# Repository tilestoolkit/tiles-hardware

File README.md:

# IoT Squares 

Squares are tiny stickers with electronics that give superpowers to everyday objects. They implement a set of physical interaction primitives.

Squares are part of Tiles, an inventor toolbox to support the design and making of interactive objects for learning and play. For more information tilestoolkit.io

This work is licensed under a [Creative Commons Attribution-ShareAlike 4.0 International License](https://creativecommons.org/licenses/by-sa/4.0/).

## Prototypes History

### Prototype 1
Designed by Norwegian Creation, March 2015

### Prototype 2 Rev A
Designed by Simone Mora, PCB manufacturing and partial assembly from Seeedstudio Fusion Service, November 2015
#### Note: 
* Bug in board design, shortcut between VDD and SDA lines

### Prototype 2 Rev B
Designed by Simone Mora, never produced.
#### Note: 
* Fixed Rev A bugs

### Prototype 2 Rev C
Designed by Simone Mora, PCB manufacturing and partial assembly from Seeedstudio Fusion Service, April 2016
#### Note: 
* Removed touch controller MPR121
* Swapped components no longer available from Seed CPL

### Prototype 2 Rev D
Designed by Simone Mora, PCB manufacturing and partial assembly from Macrofab, November 2016
#### Note:
* Moved from SMD to DIP programming header
* Swapped components not available on Macrofab common parts library
* Added Seeed GROVE I2C connector

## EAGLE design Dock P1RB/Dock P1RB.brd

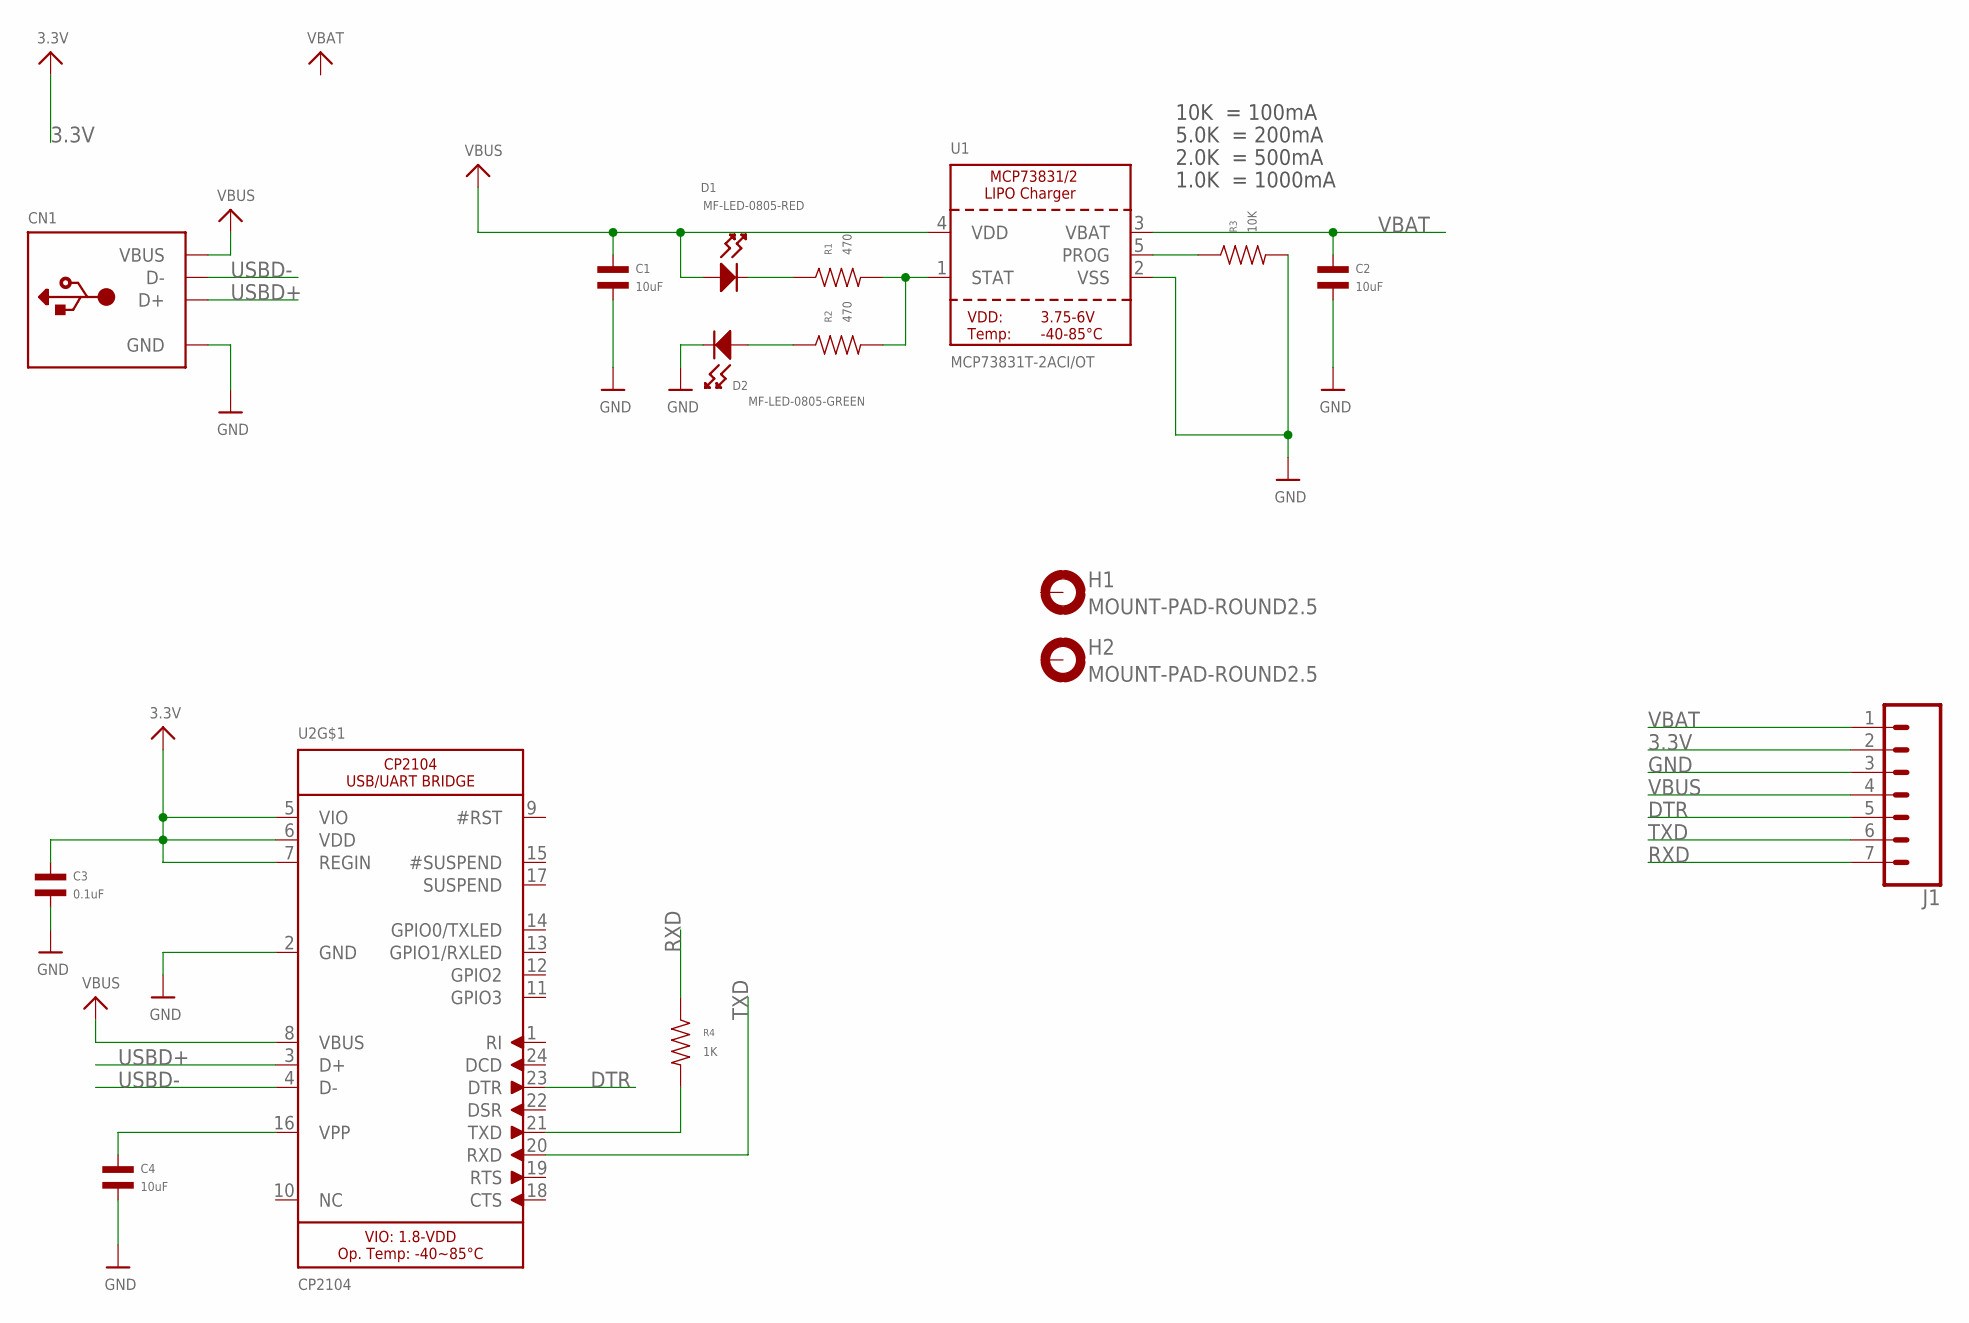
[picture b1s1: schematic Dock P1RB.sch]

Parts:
C1, C2, C4: 10uF; C1206; MPN MF-CAP-1206-10uF
C3: 0.1uF; C0603; MPN MF-CAP-0603-0.1uF
CN1: USB_TYPEAPCB; USBA_PCB
D1: MF-LED-0805-RED; LED0805
D2: MF-LED-0805-GREEN; LED0805
H1, H2: MOUNT-PAD-ROUND2.5; 2,5-PAD-SIM
J1: CONN_07; 1X07
R1, R2: 470; R0603; MPN MF-RES-0603-470
R3: 10K; R0603; MPN MF-RES-0603-10K
R4: 1K; R0603; MPN MF-RES-0603-1K
U1: MCP73831T-2ACI/OT; SOT23-5; MPN MCP73831T-2ACI/OT
U2: CP2104; QFN24_4MM_SMSC; MPN CP2104

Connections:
3.3V: C3.P$1, J1.2, U2.5 (VIO), U2.6 (VDD), U2.7 (REGIN)
DTR: J1.5, U2.23 (DTR)
GND: C1.P$2, C2.P$2, C3.P$2, C4.P$2, CN1.GND, D2.CATHODE, J1.3, R3.P$2, U1.2 (VSS), U2.2 (GND)
unnamed: D1.CATHODE, R1.P$1
unnamed: R1.P$2, R2.P$2, U1.1 (STAT)
unnamed: C4.P$1, U2.16 (VPP)
unnamed: R3.P$1, U1.5 (PROG)
unnamed: D2.ANODE, R2.P$1
unnamed: R4.P$2, U2.21 (TXD)
RXD: J1.7, R4.P$1
TP: U2.THERM (TP)
TXD: J1.6, U2.20 (RXD)
USBD+: CN1.USB_PLUS (D+), U2.3 (D+)
USBD-: CN1.USB_NEG (D-), U2.4 (D-)
VBAT: C2.P$1, J1.1, U1.3 (VBAT)
VBUS: C1.P$1, CN1.VCC (VBUS), D1.ANODE, J1.4, U1.4 (VDD), U2.8 (VBUS)

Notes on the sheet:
10K = 100mA
5.0K = 200mA
2.0K = 500mA
1.0K = 1000mA

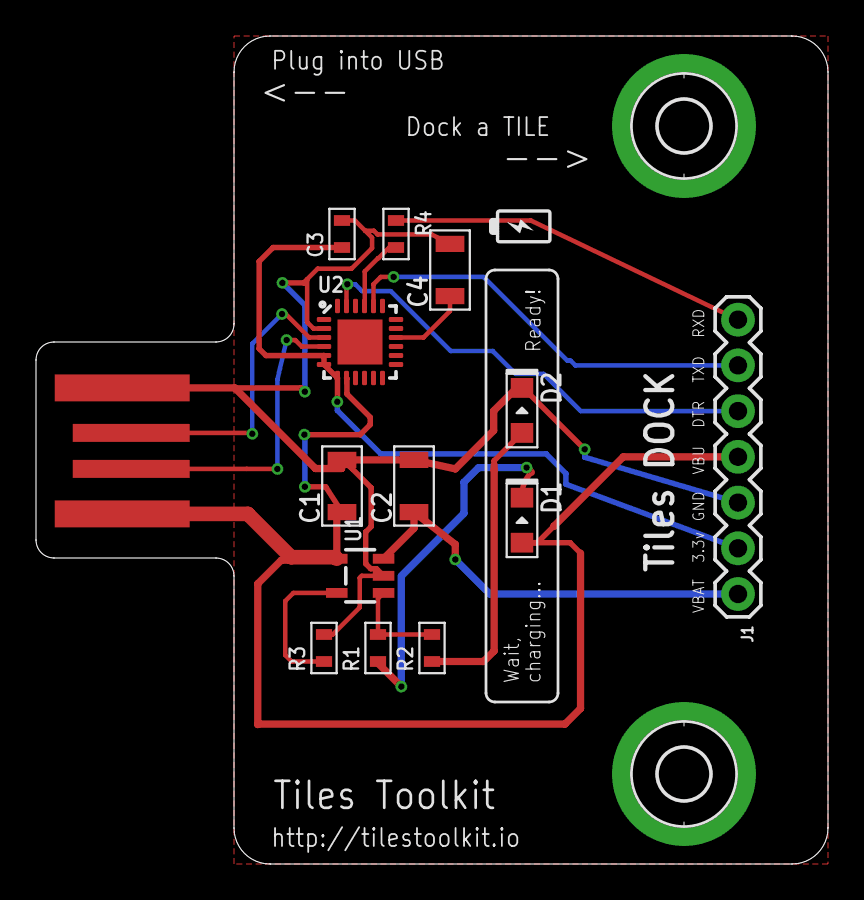
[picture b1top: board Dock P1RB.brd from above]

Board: 2 copper layers, 44.0 x 46.0 mm, 16 parts (0 on the bottom side), 15 nets.

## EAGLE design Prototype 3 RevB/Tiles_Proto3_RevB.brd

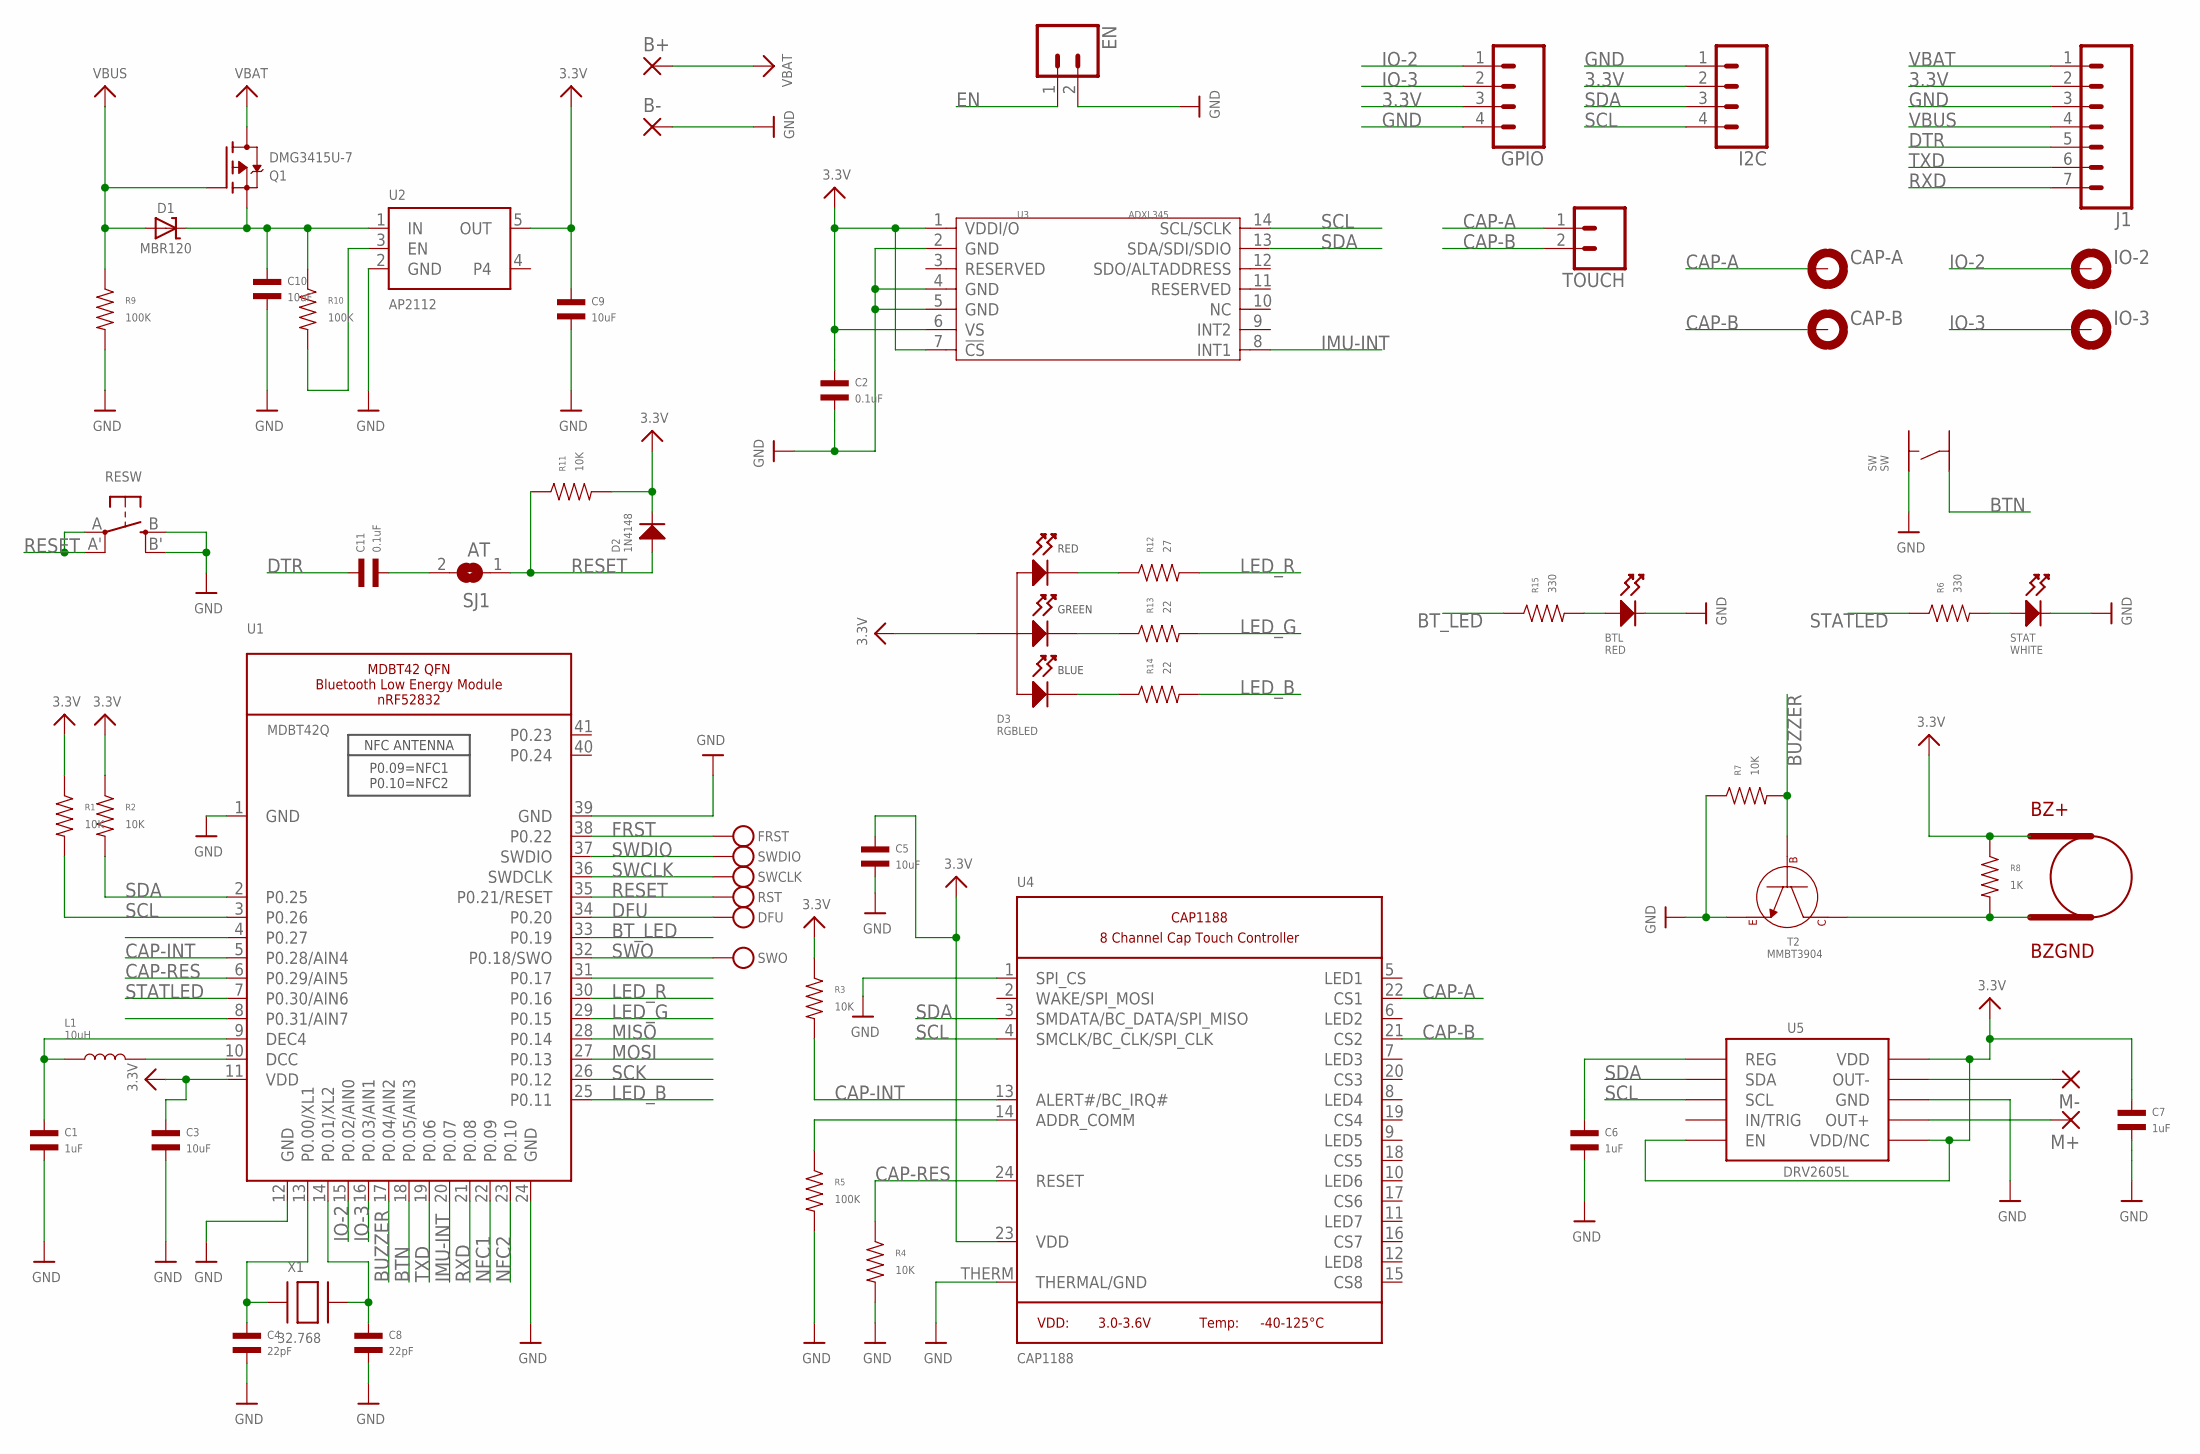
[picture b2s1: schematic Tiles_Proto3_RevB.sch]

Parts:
B+: SMD2; SMD1,27-2,54
B-: SMD2; SMD1,27-2,54
BTL: RED; LED0603
BUZZER: 4MBUZ; BUZPKG; MPN 490-CMT-4023S-SMT-TR
C1, C6, C7: 1uF; C0603; MPN MF-CAP-0603-1uF
C2, C11: 0.1uF; C0603; MPN MF-CAP-0603-0.1uF
C3, C5, C9, C10: 10uF; C1206; MPN MF-CAP-1206-10uF
C4, C8: 22pF; C0603; MPN MF-CAP-0603-22pF
CAP-A: MOUNT-PAD-ROUND2.5; 2,5-PAD-SIM
CAP-B: MOUNT-PAD-ROUND2.5; 2,5-PAD-SIM
D1: MBR120; SOD-123; MPN MBR120LSFT1G
D2: 1N4148; SOD-123
D3: RGBLED; PLCC4
DFU: TESTPOINTROUND2MM; TESTPOINT_ROUND_2MM
EN: CONN_021X02_NO_SILK; 1X02_NO_SILK
FRST: TESTPOINT1.5X2.0MM_NOCREAM; PAD-1.5X2.0
GPIO: CONN_041X04_NO_SILK; 1X04_NO_SILK
I2C: CONN_04_SIM1X04_NO_SILK; 1X04_NO_SILK_LNG
IO-2, IO-3: MOUNT-PAD-ROUND2.5; 2,5-PAD-SIM
J1: CONN_07; 1X07
L1: 10uH; L1210; MPN MF-IND-1210-10uH
M+: 1,6/0,8
M-: 1,6/0,8
Q1: DMG3415U-7; SOT23-R; MPN MF-DSC-SOT233-BSS84
R1, R2, R3, R4, R7, R11: 10K; R0603; MPN MF-RES-0603-10K
R5, R9, R10: 100K; R0603; MPN MF-RES-0603-100K
R6, R15: 330; R0603; MPN MF-RES-0603-330
R8: 1K; R0603; MPN MF-RES-0603-1K
R12: 27; R0603; MPN MF-RES-0603-27
R13, R14: 22; R0603; MPN MF-RES-0603-22
RESW: SWITCH_TACT_SMT4.6X2.8; BTN_KMR2_4.6X2.8
RST: TESTPOINTROUND2MM; TESTPOINT_ROUND_2MM
SJ1: AT; SOLDERJUMPER_CLOSEDWIRE
STAT: WHITE; LED0603; MPN LNJ037X8ARA
SW: SW; TACT4.2MM
SWCLK: TESTPOINTROUND2MM; TESTPOINT_ROUND_2MM
SWDIO: TESTPOINTROUND2MM; TESTPOINT_ROUND_2MM
SWO: TESTPOINTROUND2MM; TESTPOINT_ROUND_2MM
T2: MMBT3904; SOT-23-3
TOUCH: CONN_021X02_NO_SILK; 1X02_NO_SILK
U1: MDBT42Q; BLE_MODULE_RAYTAC_MDBT42; MPN 317030213
U2: AP2112; SOT23-5; MPN AP2112K-3.3TRG1
U3: ADXL345; LGA14-0.8-5.0X3.0MM
U4: CAP1188; QFN24_4MM_SMSC; MPN CAP1188-1-CP-TR
U5: DRV2605L; VSSOP-10; MPN DRV2605LDGST
X1: 32.768; XTAL3215; MPN ABS07-120-32.768KHZ-T

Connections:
3.3V: BUZZER.BZ+ (BUZSIG+), C2.P$1, C3.P$1, C5.P$1, C7.P$1, C9.P$1, D2.CATHODE, D3.P$1 (ANODE), GPIO.3, I2C.2, J1.2, R1.P$1, R2.P$1, R3.P$1, R8.P$1, R11.P$2, U1.11 (VDD), U2.5 (OUT), U3.1 (VDDI/O), U3.6 (VS), U3.7 (!CS), U4.23 (VDD), U5.P$5 (EN), U5.P$6 (VDD/NC), U5.P$10 (VDD)
BTN: SW.P$3, U1.18 (P0.05/AIN3)
BT_LED: R15.P$1, U1.33 (P0.19)
BUZZER: R7.P$2, T2.P$1 (BASE), U1.17 (P0.04/AIN2)
CAP-A: CAP-A.B2,8, TOUCH.1, U4.22 (CS1)
CAP-B: CAP-B.B2,8, TOUCH.2, U4.21 (CS2)
CAP-INT: R3.P$2, U1.5 (P0.28/AIN4), U4.13 (ALERT#/BC_IRQ#)
CAP-RES: R4.P$1, U1.6 (P0.29/AIN5), U4.24 (RESET)
DFU: DFU.P$1, U1.34 (P0.20)
DTR: C11.P$1, J1.5
EN: EN.1, R10.P$2, U2.3 (EN)
FRST: FRST.P$1, U1.38 (P0.22)
GND: B-.1, BTL.CATHODE, C1.P$2, C2.P$2, C3.P$2, C4.P$2, C5.P$2, C6.P$2, C7.P$2, C8.P$2, C9.P$2, C10.P$2, EN.2, GPIO.4, I2C.1, J1.3, R4.P$2, R5.P$2, R7.P$1, R9.P$2, RESW.B (S), RESW.B' (S1), STAT.CATHODE, SW.P$1, T2.P$2 (EMITTER), U1.1 (GND), U1.12 (GND), U1.24 (GND), U1.39 (GND), U2.2 (GND), U3.2 (GND), U3.4 (GND), U3.5 (GND), U4.1 (SPI_CS), U4.THERM (THERMAL/GND), U5.P$8 (GND)
IMU-INT: U1.20 (P0.07), U3.8 (INT1)
IO-2: GPIO.1, IO-2.B2,8, U1.15 (P0.02/AIN0)
IO-3: GPIO.2, IO-3.B2,8, U1.16 (P0.03/AIN1)
LED_B: R14.P$2, U1.25 (P0.11)
LED_G: R13.P$2, U1.29 (P0.15)
LED_R: R12.P$2, U1.30 (P0.16)
MISO: U1.28 (P0.14)
MOSI: U1.27 (P0.13)
unnamed: L1.P$2, U1.10 (DCC)
unnamed: C1.P$1, L1.P$1, U1.9 (DEC4)
unnamed: R5.P$1, U4.14 (ADDR_COMM)
unnamed: BUZZER.BZ- (BUZGND), R8.P$2, T2.P$3 (COLLECTOR)
unnamed: C6.P$1, U5.P$1 (REG)
unnamed: M-.1, U5.P$9 (OUT-)
unnamed: M+.1, U5.P$7 (OUT+)
unnamed: R6.P$2, STAT.ANODE
unnamed: C4.P$1, U1.13 (P0.00/XL1), X1.P$1
unnamed: C8.P$1, U1.14 (P0.01/XL2), X1.P$2
unnamed: C10.P$1, D1.C, Q1.2 (S), R10.P$1, U2.1 (IN)
unnamed: D3.P$2 (CATHODE_RED), R12.P$1
unnamed: D3.P$3 (CATHODE_GREEN), R13.P$1
unnamed: D3.P$4 (CATHODE_BLUE), R14.P$1
unnamed: BTL.ANODE, R15.P$2
unnamed: C11.P$2, SJ1.2
NFC1: U1.22 (P0.09)
NFC2: U1.23 (P0.10)
RESET: D2.ANODE, R11.P$1, RESW.A, RESW.A' (P1), RST.P$1, SJ1.1, U1.35 (P0.21/RESET)
RXD: J1.7, U1.21 (P0.08)
SCK: U1.26 (P0.12)
SCL: I2C.4, R1.P$2, U1.3 (P0.26), U3.14 (SCL/SCLK), U4.4 (SMCLK/BC_CLK/SPI_CLK), U5.P$2 (SCL)
SDA: I2C.3, R2.P$2, U1.2 (P0.25), U3.13 (SDA/SDI/SDIO), U4.3 (SMDATA/BC_DATA/SPI_MISO), U5.P$3 (SDA)
STATLED: R6.P$1, U1.7 (P0.30/AIN6)
SWCLK: SWCLK.P$1, U1.36 (SWDCLK)
SWDIO: SWDIO.P$1, U1.37 (SWDIO)
SWO: SWO.P$1, U1.32 (P0.18/SWO)
TXD: J1.6, U1.19 (P0.06)
VBAT: B+.1, J1.1, Q1.3 (D)
VBUS: D1.A, J1.4, Q1.1 (G), R9.P$1

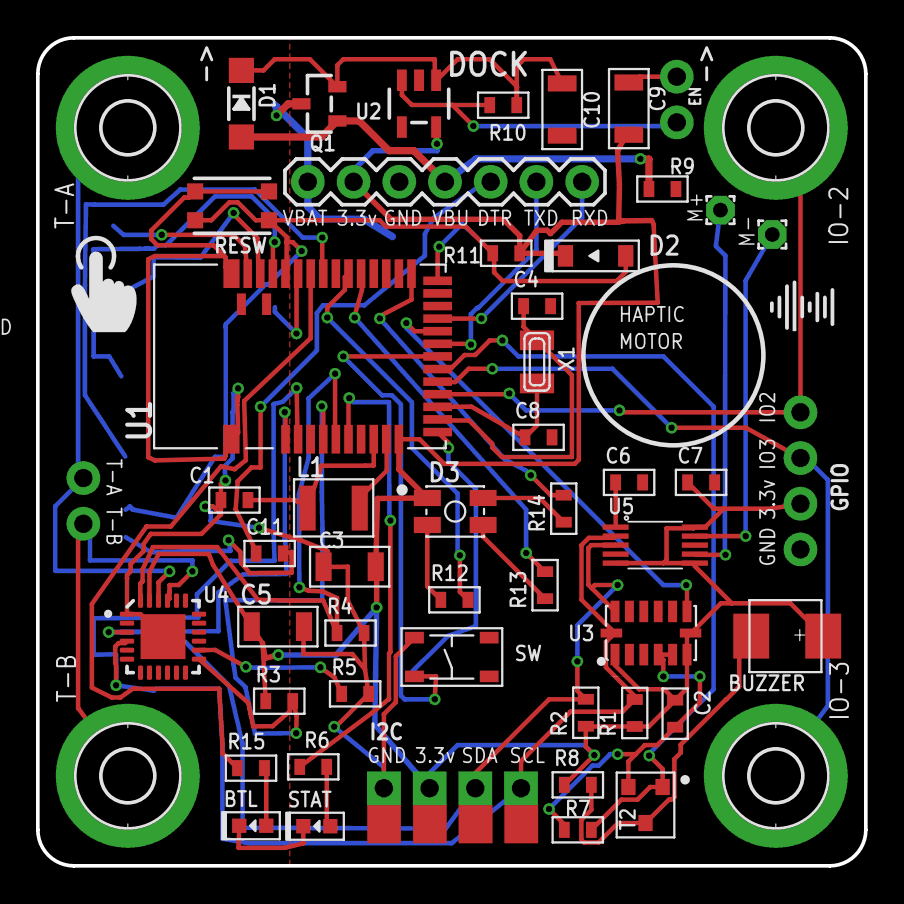
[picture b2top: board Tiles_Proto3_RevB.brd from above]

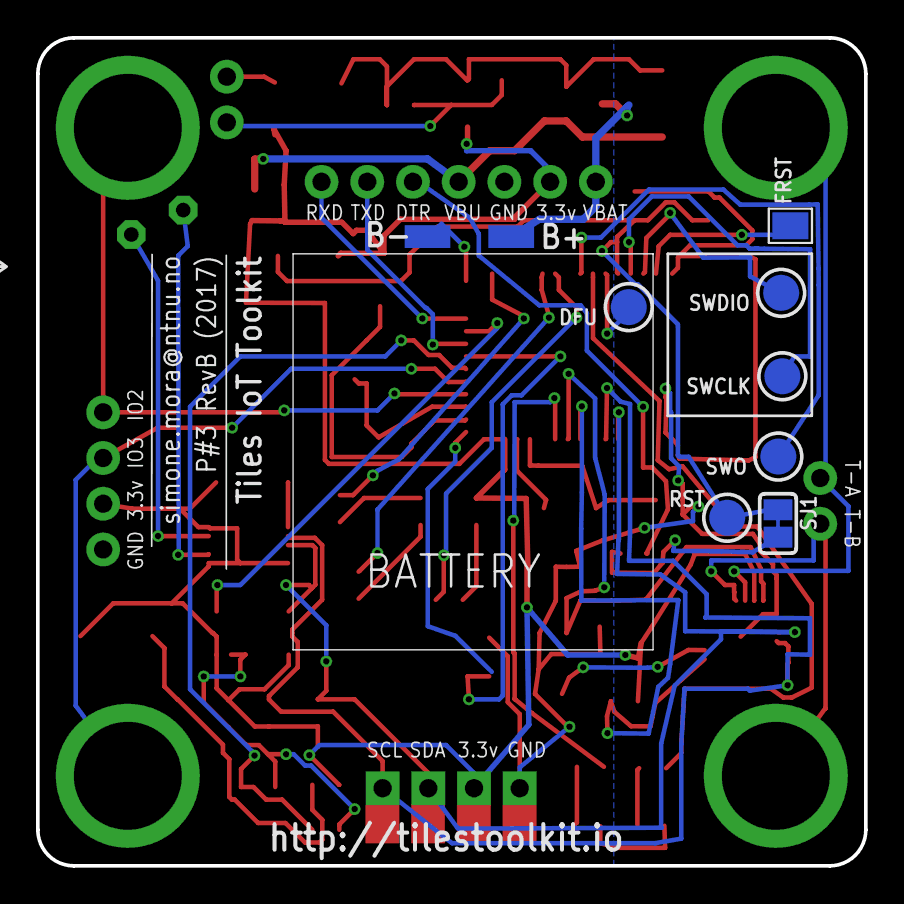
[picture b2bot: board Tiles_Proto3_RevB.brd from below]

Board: 2 copper layers, 46.0 x 46.0 mm, 63 parts (9 on the bottom side), 46 nets.

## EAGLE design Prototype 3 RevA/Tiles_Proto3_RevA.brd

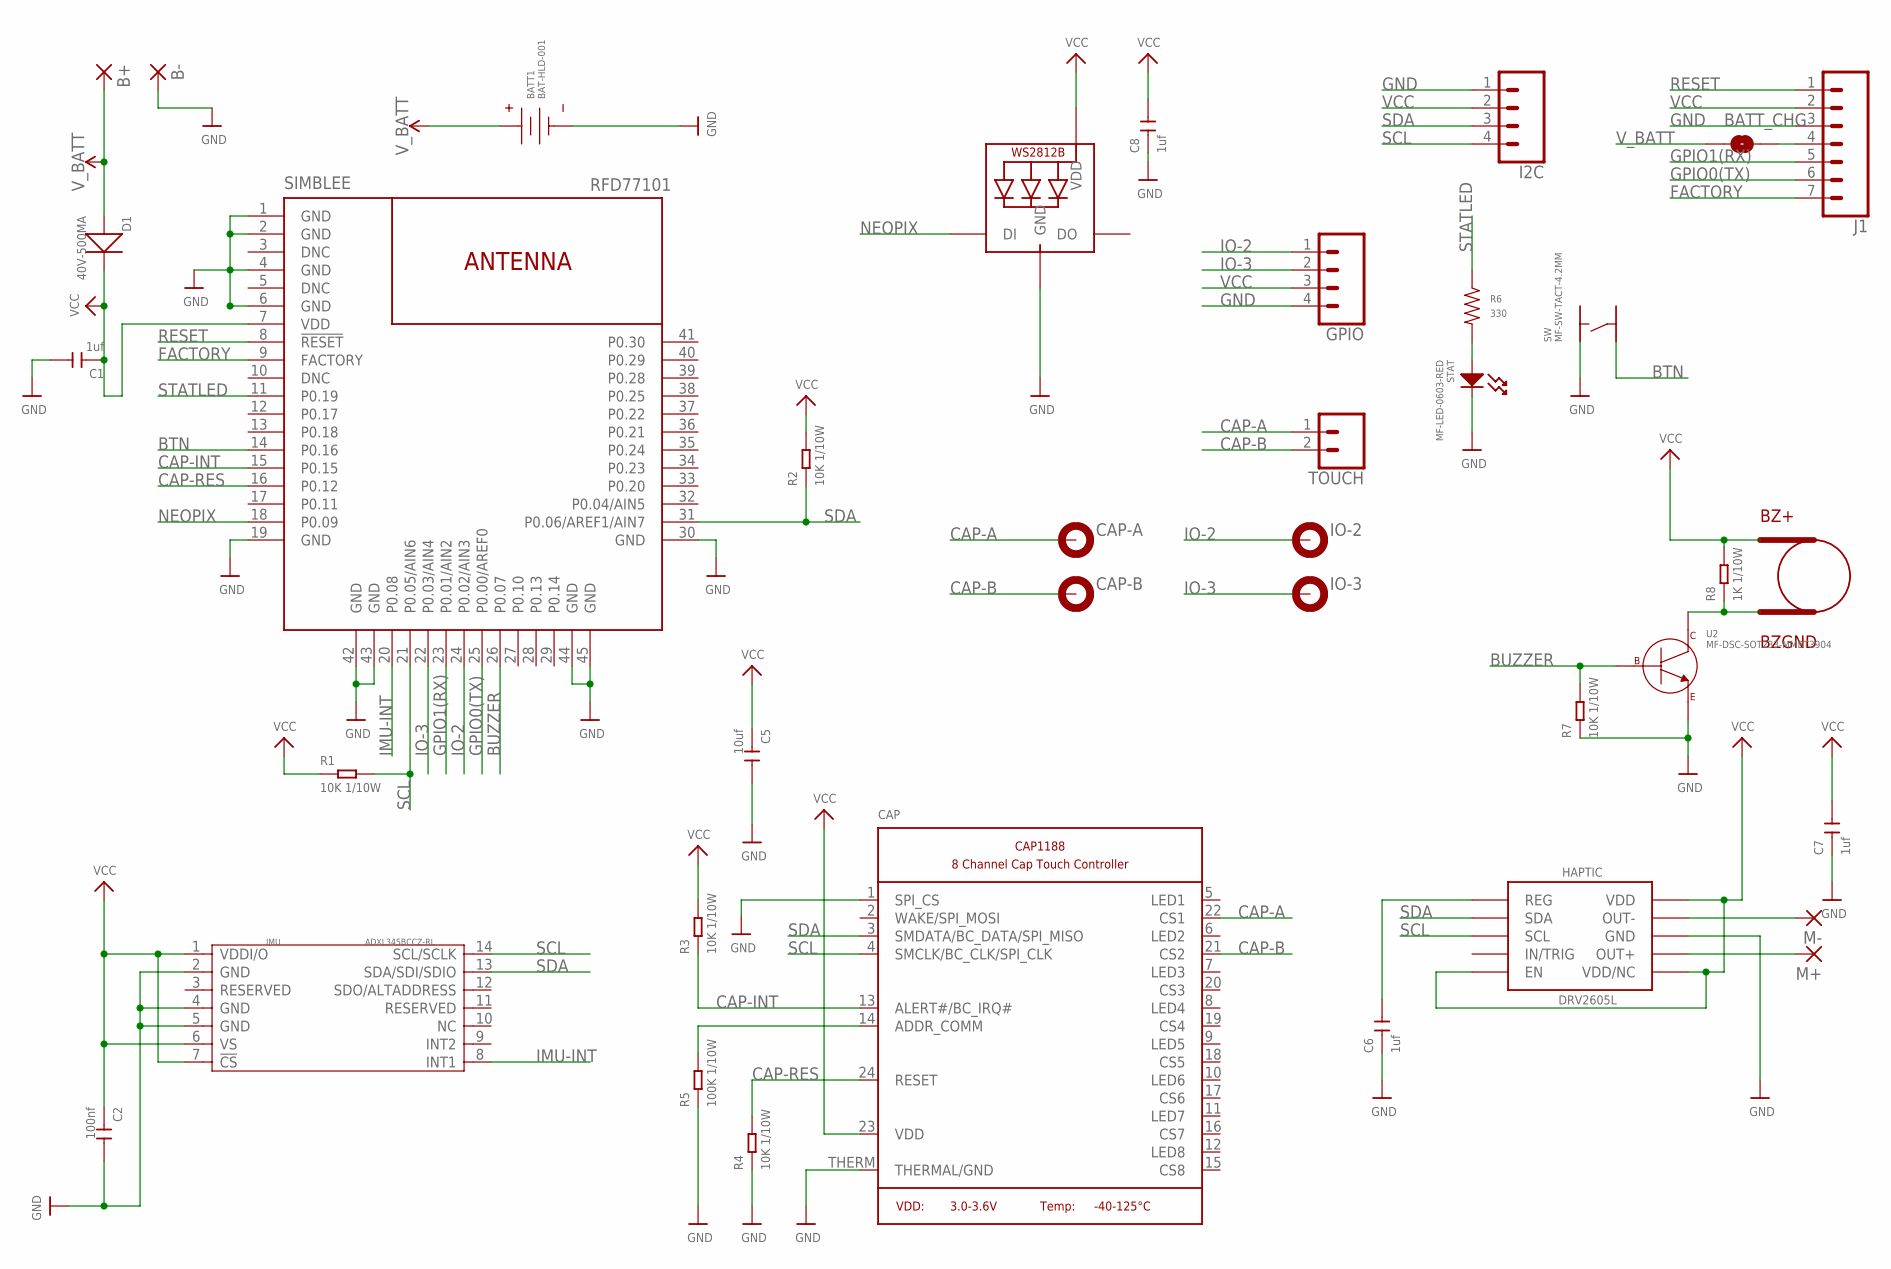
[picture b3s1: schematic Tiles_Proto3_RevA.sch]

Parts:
B+: 1,6/0,8
B-: 1,6/0,8
BATT1: BAT-HLD-001
BATT_CHG: JUMPER-SMT_2_NO_NO-SILK; SMT-JUMPER_2_NO_NO-SILK
BUZZER: 4MBUZ; BUZPKG
C1, C6, C7, C8: 1uf; C0603
C2: 100nf; C0603
C5: 10uf; C0603
CAP: CAP1188; QFN24_4MM_SMSC
CAP-A: MOUNT-PAD-ROUND2.5; 2,5-PAD-SIM
CAP-B: MOUNT-PAD-ROUND2.5; 2,5-PAD-SIM
D1: 40V-500MA; SOD-123
GPIO: CONN_041X04_NO_SILK; 1X04_NO_SILK
HAPTIC: DRV2605L; VSSOP-10
I2C: CONN_04_SIM1X04_NO_SILK; 1X04_NO_SILK_LNG
IMU: ADXL345BCCZ-RL; LGA14-0.8-5.0X3.0MM
IO-2, IO-3: MOUNT-PAD-ROUND2.5; 2,5-PAD-SIM
J1: CONN_07_SIMSQPAD_BOTTOM; 1X07_SQUAREPADS_BOTTOM
LED: WS2812B3535; LED3535
M+: 1,6/0,8
M-: 1,6/0,8
R1, R2, R3, R4, R7: 10K 1/10W; R0603
R5: 100K 1/10W; R0603
R6: 330; R0603
R8: 1K 1/10W; R0603
SIMBLEE: RFD77101
STAT: MF-LED-0603-RED; LED0603
SW: MF-SW-TACT-4.2MM; TACT4.2MM
TOUCH: CONN_021X02_NO_SILK; 1X02_NO_SILK
U2: MF-DSC-SOT233-MMBT3904; SOT-23-3

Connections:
BTN: SIMBLEE.14 (P0.16), SW.P$3
BUZZER: R7.2, SIMBLEE.26 (P0.07), U2.P$1 (BASE)
CAP-A: CAP.22 (CS1), CAP-A.B2,8, TOUCH.1
CAP-B: CAP.21 (CS2), CAP-B.B2,8, TOUCH.2
CAP-INT: CAP.13 (ALERT#/BC_IRQ#), R3.1, SIMBLEE.15 (P0.15)
CAP-RES: CAP.24 (RESET), R4.2, SIMBLEE.16 (P0.12)
FACTORY: J1.7, SIMBLEE.9 (FACTORY)
GND: B-.1, BATT1.NEG_0 (NEG), C1.2, C2.2, C5.2, C6.1, C7.1, C8.1, CAP.1 (SPI_CS), CAP.THERM (THERMAL/GND), GPIO.4, HAPTIC.P$8 (GND), I2C.1, IMU.2 (GND), IMU.4 (GND), IMU.5 (GND), J1.3, LED.4 (GND), R4.1, R5.1, R7.1, SIMBLEE.1 (GND), SIMBLEE.2 (GND), SIMBLEE.4 (GND), SIMBLEE.6 (GND), SIMBLEE.19 (GND), SIMBLEE.30 (GND), SIMBLEE.42 (GND), SIMBLEE.43 (GND), SIMBLEE.44 (GND), SIMBLEE.45 (GND), STAT.CATHODE, SW.P$1, U2.P$2 (EMITTER)
GPIO0(TX): J1.6, SIMBLEE.25 (P0.00/AREF0)
GPIO1(RX): J1.5, SIMBLEE.23 (P0.01/AIN2)
IMU-INT: IMU.8 (INT1), SIMBLEE.20 (P0.08)
IO-2: GPIO.1, IO-2.B2,8, SIMBLEE.24 (P0.02/AIN3)
IO-3: GPIO.2, IO-3.B2,8, SIMBLEE.22 (P0.03/AIN4)
unnamed: CAP.14 (ADDR_COMM), R5.2
unnamed: BUZZER.BZ- (BUZGND), R8.1, U2.P$3 (COLLECTOR)
unnamed: C6.2, HAPTIC.P$1 (REG)
unnamed: BATT_CHG.2, J1.4
unnamed: HAPTIC.P$9 (OUT-), M-.1
unnamed: HAPTIC.P$7 (OUT+), M+.1
unnamed: R6.P$2, STAT.ANODE
NEOPIX: LED.1 (DI), SIMBLEE.18 (P0.09)
RESET: J1.1, SIMBLEE.8 (!RESET!)
SCL: CAP.4 (SMCLK/BC_CLK/SPI_CLK), HAPTIC.P$2 (SCL), I2C.4, IMU.14 (SCL/SCLK), R1.2, SIMBLEE.21 (P0.05/AIN6)
SDA: CAP.3 (SMDATA/BC_DATA/SPI_MISO), HAPTIC.P$3 (SDA), I2C.3, IMU.13 (SDA/SDI/SDIO), R2.1, SIMBLEE.31 (P0.06/AREF1/AIN7)
STATLED: R6.P$1, SIMBLEE.11 (P0.19)
VCC: BUZZER.BZ+ (BUZSIG+), C1.1, C2.1, C5.1, C7.2, C8.2, CAP.23 (VDD), D1.-, GPIO.3, HAPTIC.P$5 (EN), HAPTIC.P$6 (VDD/NC), HAPTIC.P$10 (VDD), I2C.2, IMU.1 (VDDI/O), IMU.6 (VS), IMU.7 (!CS), J1.2, LED.2 (VDD), R1.1, R2.2, R3.2, R8.2, SIMBLEE.7 (VDD)
V_BATT: B+.1, BATT1.POS_0 (POS), BATT1.POS_1 (POS), BATT_CHG.1, D1.+

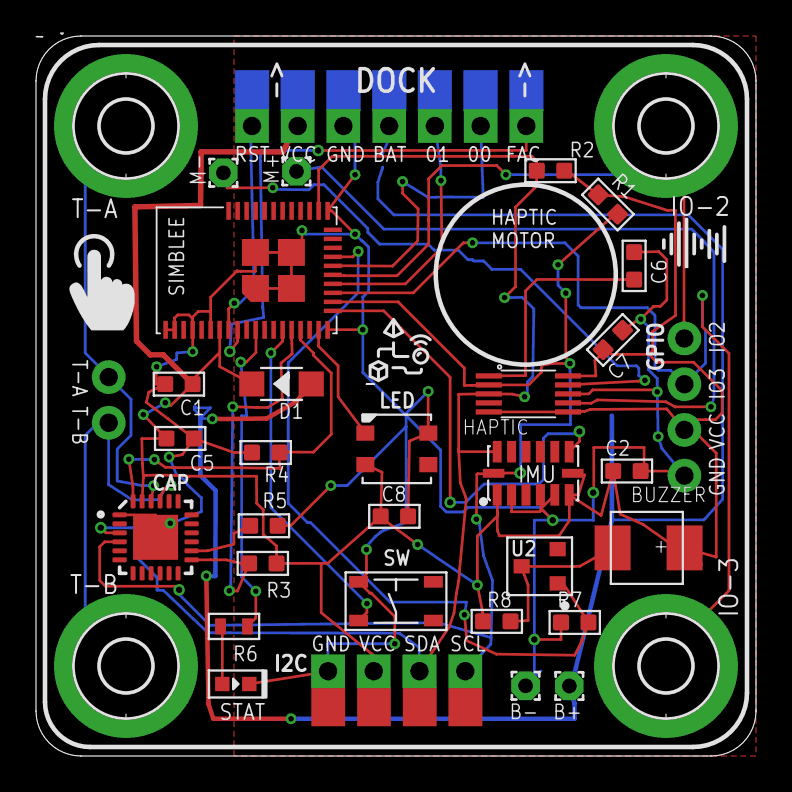
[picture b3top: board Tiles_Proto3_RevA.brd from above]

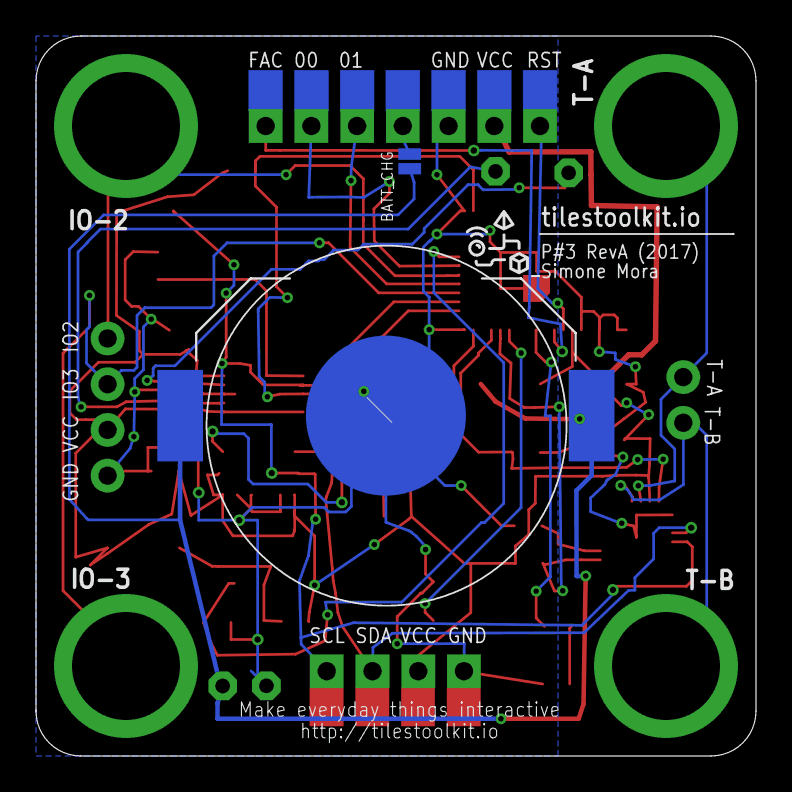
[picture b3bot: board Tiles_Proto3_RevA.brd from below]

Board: 2 copper layers, 40.0 x 40.0 mm, 38 parts (2 on the bottom side), 27 nets.

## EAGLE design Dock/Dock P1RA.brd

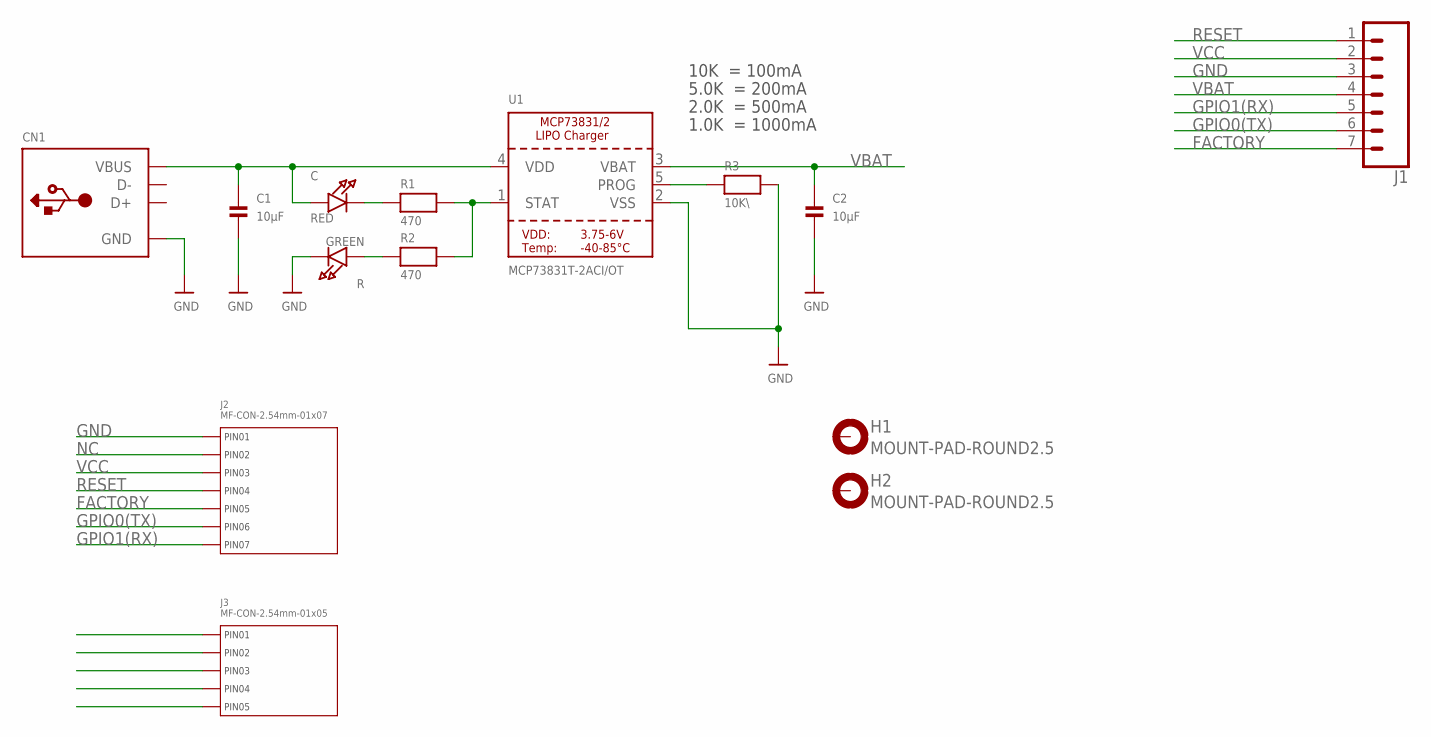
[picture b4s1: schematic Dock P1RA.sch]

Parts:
C: RED; CHIPLED_0805
C1, C2: 10µF; 1206
CN1: USB_TYPEAPCB; USBA_PCB
H1, H2: MOUNT-PAD-ROUND2.5; 2,5-PAD-SIM
J1: CONN_07_SIMSQPAD_TOP; 1X07_SQUAREPADS_TOP
J2: MF-CON-2.54mm-01x07; PTH_2.54MM_01X07
J3: MF-CON-2.54mm-01x05; PTH_2.54MM_01X05
R: GREEN; CHIPLED_0805
R1, R2: 470; 0805
R3: 10K\; 0805
U1: MCP73831T-2ACI/OT; SOT23-5

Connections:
FACTORY: J1.7, J2.P$5 (PIN5)
GND: C1.2, C2.2, CN1.GND, J1.3, J2.P$1 (PIN1), R.C, R3.2, U1.2 (VSS)
GPIO0(TX): J1.6, J2.P$6 (PIN6)
GPIO1(RX): J1.5, J2.P$7 (PIN7)
unnamed: C.C, R1.1
unnamed: R1.2, R2.2, U1.1 (STAT)
unnamed: R3.1, U1.5 (PROG)
unnamed: R.A, R2.1
NC: J2.P$2 (PIN2)
RESET: J1.1, J2.P$4 (PIN4)
VBAT: C2.1, J1.4, U1.3 (VBAT)
VCC: J1.2, J2.P$3 (PIN3)
VDD: C.A, C1.1, CN1.VCC (VBUS), U1.4 (VDD)

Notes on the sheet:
10K = 100mA
5.0K = 200mA
2.0K = 500mA
1.0K = 1000mA

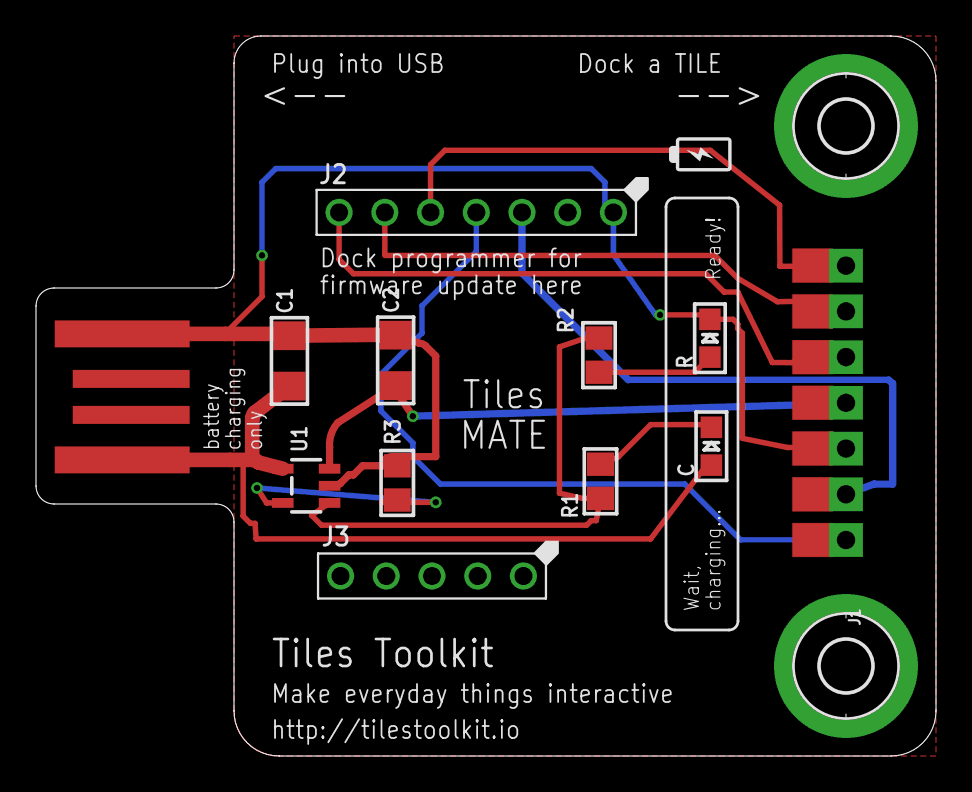
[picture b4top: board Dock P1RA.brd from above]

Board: 2 copper layers, 50.0 x 40.0 mm, 14 parts (0 on the bottom side), 12 nets.

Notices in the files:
parts and their libraries:
microbuilder: This work is placed in the public domain, and may be freely used for commercial and non-commercial work with the following conditions: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
SparkFun-Connectors: Licensing: Creative Commons ShareAlike 4.0 International - https://creativecommons.org/licenses/by-sa/4.0
